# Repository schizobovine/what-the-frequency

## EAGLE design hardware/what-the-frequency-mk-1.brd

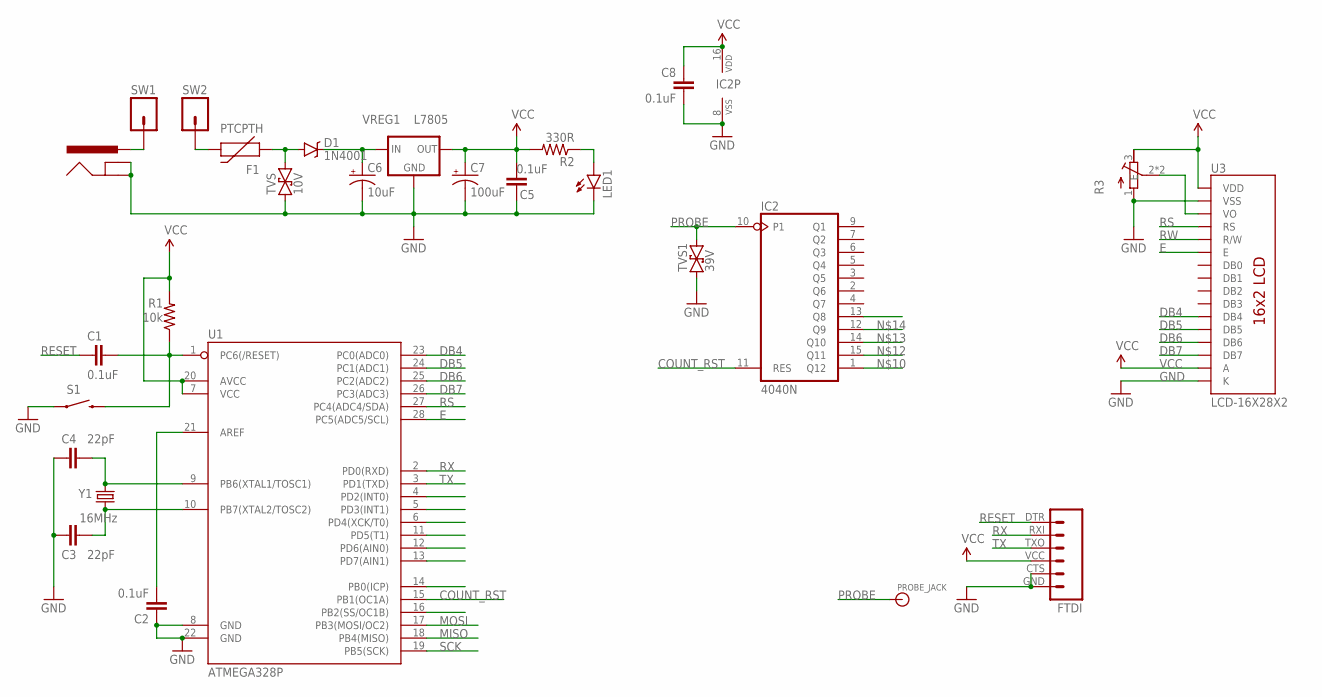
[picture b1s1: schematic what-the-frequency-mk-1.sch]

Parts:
C1, C2, C5, C8: 0.1uF; C025-024X044
C3, C4: 22pF; C025-024X044
C6: 10uF; E2,5-5
C7: 100uF; E2,5-5
D1: 1N4001; DO-41
F1: PTCPTH; PTC
FTDI: FTDI_BASICPTH-TINY-TEXT; FTDI_TINY_TXT
IC2: 4040N; DIL16
J2: POWER_JACKPTH; POWER_JACK_PTH
LED1: LED3MM
PROBE_JACK: BANANA_CONNPTH-RA; BANANA-PTH-RA-SAFEWORD
R1: 10k; AXIAL-PTH-5.08MM
R2: 330R; AXIAL-PTH-5.08MM
R3: POTENTIOMETERTHUMBWHEEL-16MM; POT-THUMBWHEEL
S1: SWITCH-MOMENTARY-2PTH-RA; TACTILE-PTH-SIDE
SW1, SW2: M01PTH_2MM; 1X01_2MM
TVS: 10V; DO-41-TVS
TVS1: 39V; DO-41-TVS
U1: ATMEGA328P; DIL28-3
U3: LCD-16X28X2; LCD-8X2
VREG1: L7805; TO-92-AMMO
Y1: 16MHz; HC49U-V

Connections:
COUNT_RST: IC2.11 (RES), U1.15 (PB1(OC1A))
DB4: U1.23 (PC0(ADC0)), U3.11 (DB4)
DB5: U1.24 (PC1(ADC1)), U3.12 (DB5)
DB6: U1.25 (PC2(ADC2)), U3.13 (DB6)
DB7: U1.26 (PC3(ADC3)), U3.14 (DB7)
E: U1.28 (PC5(ADC5/SCL)), U3.6 (E)
GND: C2.1, C3.2, C4.2, C5.1, C6.-, C7.-, C8.1, FTDI.CTS (5), FTDI.GND (6), IC2.8 (VSS), J2.GND, J2.GNDBREAK, LED1.K (C), R3.1 (A), S1.1, TVS.P$1 (1), TVS1.P$1 (1), U1.8 (GND), U1.22 (GND), U3.1 (VSS), U3.16 (K), VREG1.2 (GND)
MISO: U1.18 (PB4(MISO))
MOSI: U1.17 (PB3(MOSI/OC2))
unnamed: C6.+, D1.C, VREG1.1 (IN)
unnamed: LED1.A, R2.P$1 (1)
unnamed: J2.PWR, SW1.1
unnamed: D1.A, F1.P$1 (1), TVS.P$2 (2)
unnamed: F1.P$2 (2), SW2.1
unnamed: C4.1, U1.9 (PB6(XTAL1/TOSC1)), Y1.2
unnamed: C3.1, U1.10 (PB7(XTAL2/TOSC2)), Y1.1
unnamed: C2.2, U1.21 (AREF)
unnamed: R3.2 (S), R3.2@1 (S), U3.3 (VO)
unnamed: C1.2, R1.P$1 (1), S1.2, U1.1 (PC6(/RESET))
PROBE: IC2.10 (P1), PROBE_JACK.P$1, PROBE_JACK.P$2, TVS1.P$2 (2)
RESET: C1.1, FTDI.DTR (1)
RS: U1.27 (PC4(ADC4/SDA)), U3.4 (RS)
RW: U3.5 (R/W)
RX: FTDI.RXI (2), U1.2 (PD0(RXD))
SCK: U1.19 (PB5(SCK))
TX: FTDI.TXO (3), U1.3 (PD1(TXD))
VCC: C5.2, C7.+, C8.2, FTDI.VCC (4), IC2.16 (VDD), R1.P$2 (2), R2.P$2 (2), R3.3 (E), U1.7 (VCC), U1.20 (AVCC), U3.2 (VDD), U3.15 (A), VREG1.3 (OUT)

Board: 2 copper layers, 27 parts (1 on the bottom side), 23 nets, no tracks yet.

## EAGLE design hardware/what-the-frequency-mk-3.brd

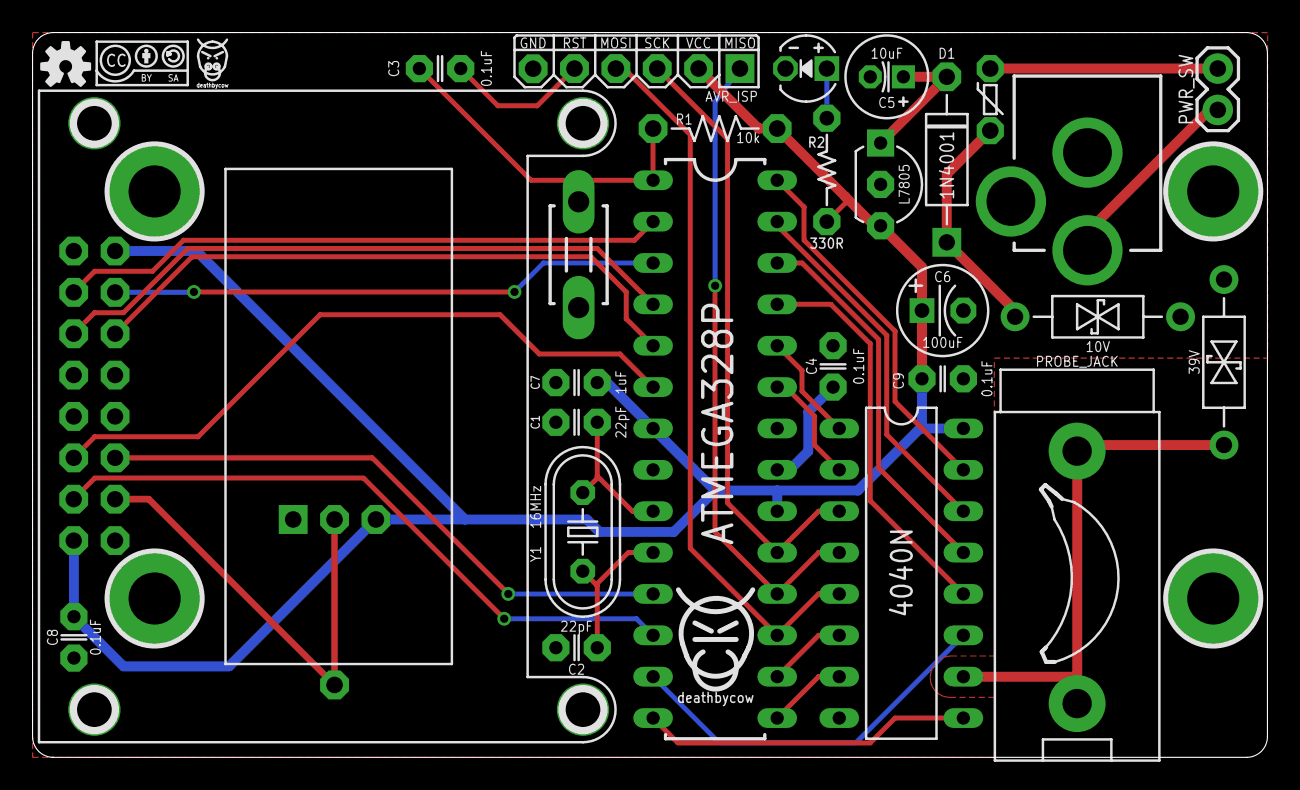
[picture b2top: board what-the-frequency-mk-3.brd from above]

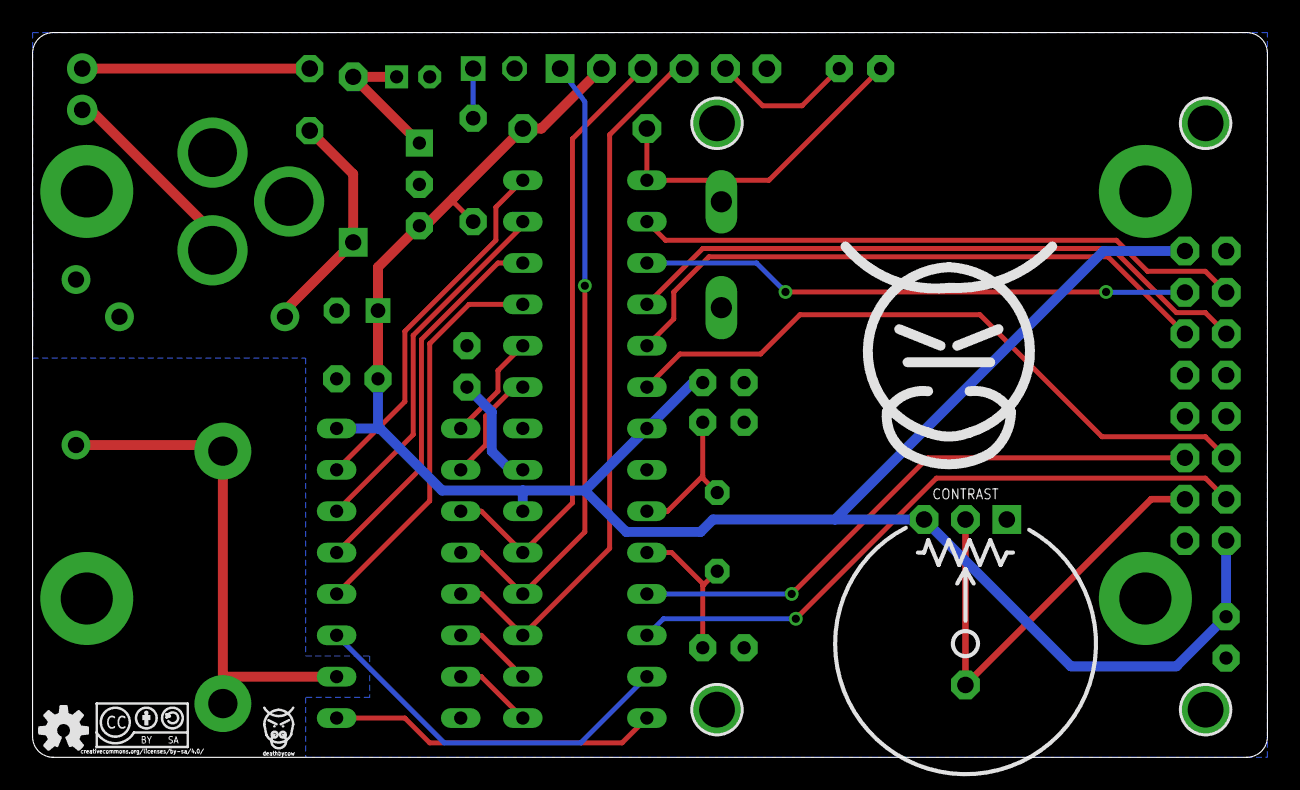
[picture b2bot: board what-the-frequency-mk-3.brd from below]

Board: 2 copper layers, 75.8 x 44.5 mm, 39 parts (5 on the bottom side), 34 nets.

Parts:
C1, C2: 22pF; C025-024X044
C3, C4, C8, C9: 0.1uF; C025-024X044
C5: 10uF; E2-5
C6: 100uF; E2,5-6
C7: 1uF; C025-024X044
CONTRAST: POT-THUMBWHEEL
D1: 1N4001; DO-41
F1: PTCPTH; PTC
H1, H2, H3, H4: HOLE#4; HOLE-#4
IC1: 4040N; DIL16
J1: POWER_JACKPTH; POWER_JACK_PTH
J2: AVR_ISP; AVR_MINI_PROG
LED1: LED3MM
PROBE_JACK: BANANA-PTH-RA-SAFEWORD
PWR_SW: M02PTH; 1X02
R1: 10k; RESISTOR-AXIAL-PTH-7.68MM
R2: 330R; RESISTOR-AXIAL-PTH-5.08MM
S1: DTS-3
TVS: 10V; DO-41-TVS
TVS1: 39V; DO-41-TVS
U1: ATMEGA328P; DIL28-3
U2: LCD-16X28X2; LCD-8X2
U$1: COW_SMALL
U$2, U$4: OSHW-LOGO-S
U$3: CC-BY-SA-4.0URL-BOTTOM; CC-BY-SA-4.0-URL-BOTTOM
U$5, U$6: COW_SMALLER
U$7: CC-BY-SA-4.0NO-URL; CC-BY-SA-4.0-NO-URL
U$8: COW
VREG1: L7805; TO-92-AMMO
Y1: 16MHz; HC49U-V

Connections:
CNT1: IC1.9, U1.14
CNT2: IC1.7, U1.15
CNT3: IC1.6, U1.16
CNT4: IC1.5, J2.4, U1.17
CNT5: IC1.3, J2.3, U1.19
CNT6: IC1.2, U1.23
CNT7: IC1.4, J2.1, U1.18
CNT8: IC1.13, U1.26
CNT9: IC1.12, U1.25
CNT10: IC1.14, U1.27
CNT11: IC1.15, U1.28
CNT12: IC1.1, U1.24
CNT_RST: IC1.11, U1.13
DB4: U1.5, U2.11
DB5: U1.4, U2.12
DB6: U1.3, U2.13
DB7: U1.2, U2.14
E: U1.6, U2.6
GND: C1.2, C2.2, C4.1, C5.-, C6.-, C7.1, C8.1, C9.1, CONTRAST.1, IC1.8, J1.GND, J1.GNDBREAK, J2.6, LED1.K, S1.1, TVS.P$1, TVS1.P$1, U1.8, U1.22, U2.1, U2.7, U2.8, U2.9, U2.10, U2.16, VREG1.2
unnamed: C5.+, D1.C, VREG1.1
unnamed: LED1.A, R2.P$1
unnamed: J1.PWR, PWR_SW.1
unnamed: D1.A, F1.P$1, TVS.P$2
unnamed: F1.P$2, PWR_SW.2
unnamed: C1.1, U1.9, Y1.2
unnamed: C2.1, U1.10, Y1.1
unnamed: C4.2, U1.21
unnamed: CONTRAST.2, CONTRAST.2@1, U2.3
unnamed: C3.2, R1.P$1, S1.2, U1.1
PROBE: IC1.10, PROBE_JACK.P$1, PROBE_JACK.P$2, TVS1.P$2
RS: U1.12, U2.4
RST: C3.1, J2.5
RW: U1.11, U2.5
VCC: C6.+, C7.2, C8.2, C9.2, CONTRAST.3, IC1.16, J2.2, R1.P$2, R2.P$2, U1.7, U1.20, U2.2, U2.15, VREG1.3

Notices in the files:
parts and their libraries:
SparkFun-DigitalIC: Licensing: Creative Commons ShareAlike 4.0 International - https://creativecommons.org/licenses/by-sa/4.0
A_butts: creativecommons.org/licenses/by-sa/4.0
